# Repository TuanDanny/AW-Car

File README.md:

# AW-Car

Xe 4WD hai bên độc lập. **Web → Motion → SPI → Tang Nano9K → DRV8833** là
đường điều khiển trực tiếp. Brain chạy Xiaozhi, mic, loa và OLED, rồi gửi lệnh
AI sang Motion qua UART. Manual hoạt động qua AW-CAR tại `192.168.4.1`.
Wi-Fi router phục vụ Xiaozhi, OTA và log.

[Bản hiện hành, mốc nghiệm thu và phần cứng chờ bổ sung](docs/current-release.md)
ghi mã nguồn và mã firmware của cả ba board. `main` là nhánh chính thức.
`prototype-v1` và `prototype-v2` là hai mốc phục hồi.

| Thư mục | Nội dung |
| --- | --- |
| [esp](esp/README.md) | Firmware Brain, Motion và giao thức C++ dùng chung |
| [fpga](fpga/README.md) | SPI, PWM và encoder SystemVerilog trên Tang Nano9K |
| [schematic](schematic/README.md) | Bản vẽ đấu nối tham chiếu |
| [docs](docs/README.md) | Hướng dẫn, contract và lịch sử kiểm chứng |
| [data](data/README.md) | Vector giao thức và bằng chứng đã lọc |
| [utils](utils/README.md) | Build, kiểm tra, OTA và thu log |
| [test](test/README.md) | Kiểm thử host, trình duyệt và RTL |

Bắt đầu từ [Dashboard](docs/dashboard.md), [OTA và log](docs/ota-usage.md)
hoặc [hướng dẫn build](docs/build.md). Đọc [contract](docs/protocol.md)
trước khi đổi giao thức và [bảng chân đang chạy](docs/current-release.md#chân-cảm-biến-và-phần-cứng-chờ-bổ-sung)
trước khi đi dây.

## Bảng kết nối toàn mạch

Bảng V4 dưới đây đối chiếu với PCB và schematic **candidate** đang chỉnh tại
`schematic/pcb-in/ban-di-day-dang-do` trên máy làm việc ngày 26/11/2026.
PCB này còn đang đi dây và chưa được kiểm chứng hoàn chỉnh.\nPCB chính thức trên máy nằm trong thư mục `schematic/pcb-in/ban-di-day-dang-do`. Số `Pxx` là số
chân package FPGA của Tang Nano 9K, còn `GPIOxx` là GPIO ESP32-S3.

**Trạng thái V4:** source trên nhánh này sử dụng pinout PCB V4 ở SPI
Motion, encoder và các đầu ra DRV. Firmware V4 mới build cần được thử lại
trên đúng ba board trước khi xác nhận trùng với Flash trên xe.

### Nguồn

| Đầu nối hoặc nguồn | Kết nối V4 |
| --- | --- |
| U15 | Chân 1: +5,18 V từ DSN 1 cho Brain và Motion. Chân 2: GND. |
| U16 | Chân 1: +5,10 V từ DSN 2 cho Tang, MAX98357A và tải 5 V AUX. Chân 2: GND. |
| U18 | Chân 1: +3,3 V từ buck ngoại vi. Chân 2: GND. Cấp các module ngoại vi 3,3 V theo bảng dưới. |
| J9 | Chân 1: +VM từ pin 2S qua cầu chì F1 ngoài bo. Chân 2: GND. VM đến cả hai DRV. |
| GND | Âm pin, âm các buck, ba board và ngoại vi nối chung. Hai đầu ra dương 5 V và buck 3,3 V giữ riêng. |

Buck 3,3 V cấp ngoại vi, không cấp vào chân 3V3 hoặc GPIO ESP32-S3.
Ngắt nguồn 5 V ngoài của board trước khi cắm USB board đó.

### Brain và Motion

| Tín hiệu | Nối dây |
| --- | --- |
| Brain TX → Motion RX | Brain GPIO17 → Motion GPIO14 |
| Motion TX → Brain RX | Motion GPIO13 → Brain GPIO18 |
| INMP441 WS / SCK / SD | Brain GPIO4 / GPIO5 / GPIO6 |
| INMP441 VDD / GND / L/R | 3,3 V ngoại vi / GND / GND |
| OLED SDA / SCL | Brain GPIO41 / GPIO42. VCC 3,3 V ngoại vi và GND. |
| MAX98357A DIN / BCLK / LRC | Brain GPIO7 / GPIO15 / GPIO16 |
| MAX98357A VIN / GND | 5 V AUX / GND |
| Loa | Nối hai dây vào SPK+ và SPK− của MAX98357A. |
| VL53L0X SDA / SCL | Motion GPIO11 / GPIO12, VCC 3,3 V ngoại vi và GND |
| MPU SDA / SCL | Motion GPIO6 / GPIO7, VCC 3,3 V ngoại vi và GND |
| Mép trái / phải theo firmware main | Motion GPIO8 / GPIO9. Trên PCB V4 hai chân này đưa ra JXM1. |
| STBY hai DRV | Motion GPIO10 qua hai nhánh điện trở riêng tới STBY trái và phải |

GPIO17/18 của Motion được ghi nhận là hỏng trên board đã dùng. Nút BOOT
Brain là GPIO0, LED onboard Brain là GPIO48.

### SPI Motion → Tang

| Tín hiệu | Motion | Tang |
| --- | --- | --- |
| MOSI | GPIO42 | P25 |
| MISO | GPIO41 | P26 |
| SCLK | GPIO40 | P29 |
| CS | GPIO39 | P30 |

### Tang, DRV và encoder

| Tín hiệu | Chân Tang V4 |
| --- | --- |
| DRV trái IN1 / IN2 | P51 / P35 |
| DRV phải IN1 / IN2 | P31 / P32 |
| Encoder trái / phải qua chuyển mức | P49 / P48 |

Trên PCB V4, IN1 nối đến AIN1 và BIN1 cùng phía, IN2 nối đến AIN2 và BIN2.
Mỗi DRV có hai ngõ ra AO và BO cho hai motor của cùng bên. Mỗi encoder dùng
một OUT, qua bộ chuyển mức từ 5 V encoder sang mức tham chiếu 3,3 V của Tang.
Giắc encoder U10/U17 có thứ tự GND, 5 V AUX, OUT. Xác nhận thứ tự trên module
encoder thực tế trước khi cắm.

### Giắc mở rộng trên PCB V4

| Giắc | Thứ tự chân theo số pad |
| --- | --- |
| JXB1 — Brain 2×5 | 1 GPIO8, 2 GPIO9, 3 GPIO10, 4 GPIO11, 5 GPIO12, 6 GPIO13, 7 GPIO14, 8 GPIO21, 9 GPIO47, 10 GPIO1 |
| JXM1 — Motion 2×6 | 1 GND, 2 3V3 ngoại vi, 3 GPIO8, 4 GPIO9, 5 GPIO38, 6 GPIO5, 7 GND, 8 SDA ToF, 9 SCL ToF, 10 GND, 11 5V AUX, 12 3V3 ngoại vi |
| JXT1 — Tang 2×5 | 1 P27, 2 P28, 3 P33, 4 P34, 5 P40, 6 P41, 7 P42, 8 P53, 9 P54, 10 P56 |

JXB1 gồm 10 chân GPIO, lấy nguồn và GND từ giắc khác. SDA/SCL trên JXM1 dùng
chung bus ToF. Một số chân JXT1 dùng chung chức năng RGB LCD trên board Tang;
cần cấu hình RTL và xem xét thiết bị gắn trên board khi sử dụng.

### Siêu âm dự kiến trên PCB V4

| Vị trí | TRIG từ Motion | ECHO tới Motion |
| --- | --- | --- |
| Trước U19 | GPIO1 | GPIO15 qua chia áp |
| Trái U20 | GPIO2 | GPIO16 qua chia áp |
| Phải U21 | GPIO21 | GPIO4 qua chia áp |

Mỗi giắc có thứ tự 5 V AUX, TRIG, ECHO, GND. Mạch ECHO chia áp trước GPIO
ESP32-S3. Các kênh này là bố trí PCB dự kiến, cần kiểm tra firmware và module
thực tế trước khi sử dụng.

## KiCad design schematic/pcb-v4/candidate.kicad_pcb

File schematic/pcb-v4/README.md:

# PCB V4 đang phát triển

[Mở project KiCad](candidate.kicad_pro)

Bản sao từ PCB ủi được lưu trên máy ngày 25/11/2026. Thiết kế đang chỉnh,
chưa đủ điều kiện chế tạo. KiCad CLI lần kiểm tra tích hợp ghi nhận 93 lỗi
clearance, 4 lỗi đường biên, 2 sai khác schematic và các cảnh báo. Cần đối chiếu
bản chỉnh tay mới nhất và khắc phục DRC, sau đó thử điện và tải thực tế.

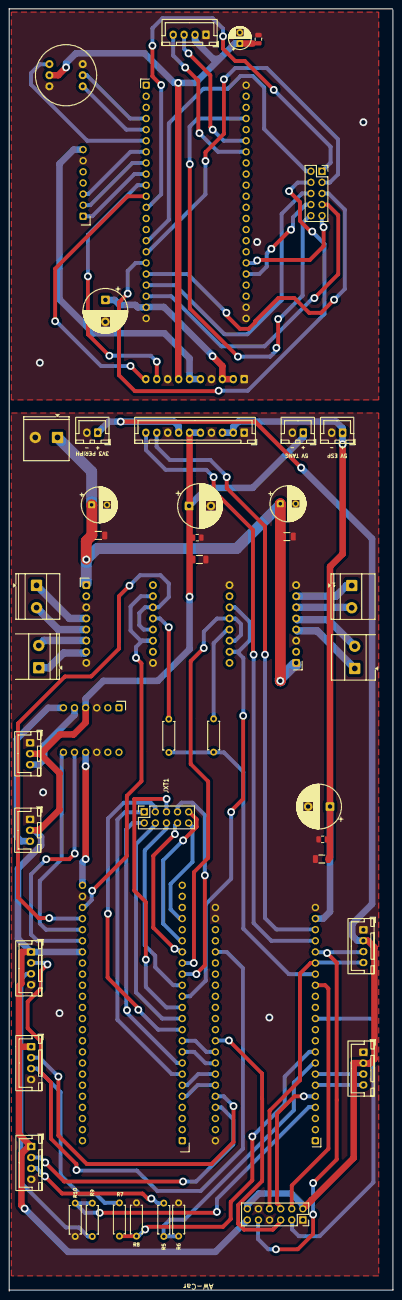
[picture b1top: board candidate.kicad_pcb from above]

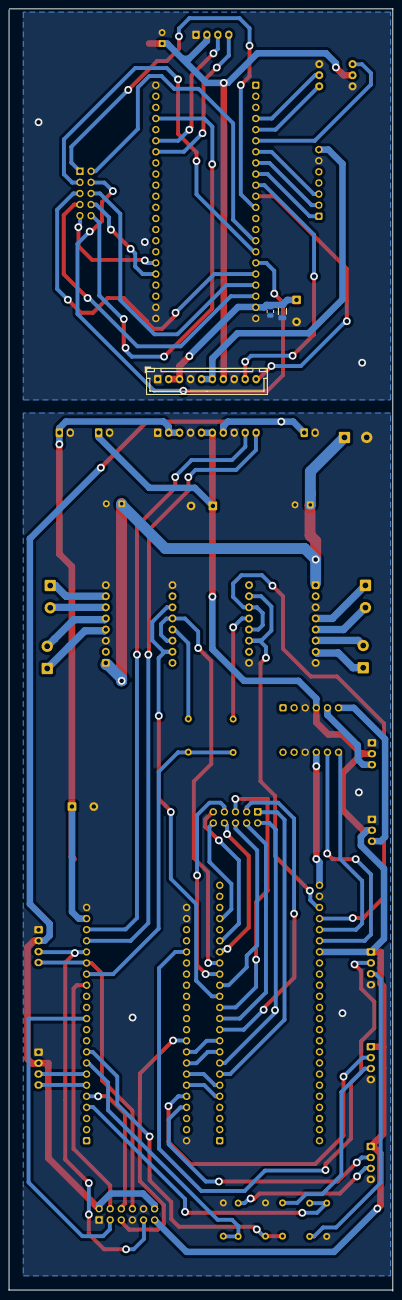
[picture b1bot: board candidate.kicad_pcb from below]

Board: 2 copper layers, 87.9 x 293.2 mm, 52 parts (3 on the bottom side), 82 nets.

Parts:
C1, C2, C3: 1000uF/16V; CP_Radial_D10.0mm_P5.00mm
C4, C5, C6: 10uF/16V; C_1206_3216Metric
C7, C8, C9: 100nF/16V; C_0805_2012Metric
C10: 47uF/10V; CP_Radial_D5.0mm_P2.50mm
C11: 100nF/10V; C_0805_2012Metric
C12, C14: 220uF/25V; CP_Radial_D8.0mm_P3.50mm
C13, C15: 10uF/25V; C_1206_3216Metric
J9: VM <= 8.4V; TerminalBlock_Phoenix_MKDS-1,5-2-5.08_1x02_P5.08mm_Horizont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
J11: M1 LF; TerminalBlock_Phoenix_MKDS-1,5-2-5.08_1x02_P5.08mm_Horizont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
J12: M2 LR; TerminalBlock_Phoenix_MKDS-1,5-2-5.08_1x02_P5.08mm_Horizont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
J13: M3 RF; TerminalBlock_Phoenix_MKDS-1,5-2-5.08_1x02_P5.08mm_Horizont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
J14: M4 RR; TerminalBlock_Phoenix_MKDS-1,5-2-5.08_1x02_P5.08mm_Horizont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
JBT1, JBT2: JST-XH 10P INTERTIER; JST_XH_B10B-XH-A_1x10_P2.50mm_Vertical
JOLED1: OLED_REMOTE_4P_3V3; JST_XH_B4B-XH-A_1x04_P2.50mm_Vertical
JXB1: BRAIN_EXP_GPIO_10P; PinSocket_2x05_P2.54mm_Vertical
JXM1: MOTION_EXP_GPIO_12P; PinSocket_2x06_P2.54mm_Vertical
JXT1: TANG_EXP_GPIO_10P; PinSocket_2x05_P2.54mm_Vertical
R1, R2: 1k; R_Axial_DIN0207_L6.3mm_D2.5mm_P7.62mm_Horizontal
R5, R7, R9: 10k; R_Axial_DIN0207_L6.3mm_D2.5mm_P7.62mm_Horizontal
R6, R8, R10: 15k; R_Axial_DIN0207_L6.3mm_D2.5mm_P7.62mm_Horizontal
U1: BRAIN; ESP32_S3_DevKitC_2x22
U2: MOTION; ESP32_S3_DevKitC_2x22
U3: TANG NANO 9K; Tang_Nano_9K_2x24
U4: DRV LEFT; DRV8833_V318_2x08
U5: DRV RIGHT; DRV8833_V318_2x08
U6: INMP441_SOCKET_2x3_VERIFY; INMP441_Module_2x03_Row7.62_14mm_PROVISIONAL
U7: MAX98357A; MAX98357A_1x07
U9: LEVEL SHIFT; Level_Shifter_2x06
U10: ENC R 5V; JST_XH_B3B-XH-A_1x03_P2.50mm_Vertical
U11: MPU; JST_XH_B4B-XH-A_1x04_P2.50mm_Vertical
U12: TOF; JST_XH_B4B-XH-A_1x04_P2.50mm_Vertical
U15: +5V ESP; JST_XH_B2B-XH-A_1x02_P2.50mm_Vertical
U16: +5V TANG/SPK; JST_XH_B2B-XH-A_1x02_P2.50mm_Vertical
U17: ENC L 5V; JST_XH_B3B-XH-A_1x03_P2.50mm_Vertical
U18: +3V3 PERIPH; JST_XH_B2B-XH-A_1x02_P2.50mm_Vertical
U19, U20, U21: HC-SR04 VCC TRIG ECHO GND; JST_XH_B4B-XH-A_1x04_P2.50mm_Vertical

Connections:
BOT_3V3_PERIPH: JBT2.7 (3V3_ngoại_vi), JXM1.2 (3V3_PERIPH_2), JXM1.12 (3V3_PERIPH_16), U11.2 (VCC_3V3), U12.2 (VIN_3V3), U18.1 (VIN+)
BOT_3V3_TANG: U3.B24 (3V3), U9.B04 (LV_3V3)
BOT_5V_AUX: C3.1, C6.1, C9.1, JBT2.5 (5V_AUX), JBT2.6 (5V_AUX), JXM1.11 (5V_AUX_14), U3.B18 (5V), U9.A04 (HV_5V), U10.2 (VCC_5V), U16.1 (VIN+), U17.2 (VCC_5V), U19.1 (VCC_5V), U20.1 (VCC_5V), U21.1 (VCC_5V)
BOT_5V_ESP_SUPPLY: C2.1, C5.1, C8.1, JBT2.2 (5V_ESP), JBT2.3 (5V_ESP), U2.A21 (5V), U15.1 (VIN+)
BOT_BM_BRAIN_TX: JBT2.9 (Brain_TX), U2.A20 (GPIO14)
BOT_BM_MOTION_TX: JBT2.10 (Motion_TX), U2.A19 (GPIO13)
BOT_ENC_L_3V3: U3.B20 (P49), U9.B06 (LV1)
BOT_ENC_L_5V: U9.A06 (HV1), U17.3 (OUT)
BOT_ENC_R_3V3: U3.B19 (P48), U9.B05 (LV2)
BOT_ENC_R_5V: U9.A05 (HV2), U10.3 (OUT)
BOT_EXP_GPIO5: JXM1.6 (GPIO5_9), U2.A05 (GPIO5)
BOT_EXP_GPIO8: JXM1.3 (GPIO8_3), U2.A12 (GPIO8)
BOT_EXP_GPIO9: JXM1.4 (GPIO9_4), U2.A15 (GPIO9)
BOT_EXP_GPIO38: JXM1.5 (GPIO38_7), U2.B10 (GPIO38)
BOT_GND: C2.2, C3.2, C5.2, C6.2, C8.2, C9.2, C12.2, C13.2, C14.2, C15.2, J9.2 (GND), JBT2.1 (GND), JBT2.4 (GND), JBT2.8 (GND), JXM1.1 (GND_1), JXM1.7 (GND_10), JXM1.10 (GND_13), R6.2, R8.2, R10.2, U2.A22 (GND), U2.B01 (GND), U2.B21 (GND), U2.B22 (GND), U3.B23 (GND), U4.A03 (GND), U4.A08 (GND), U4.B08 (GND), U5.A03 (GND), U5.A08 (GND), U5.B08 (GND), U9.A03 (GND), U9.B03 (GND), U10.1 (GND), U11.1 (GND), U12.1 (GND), U15.2 (GND), U16.2 (GND), U17.1 (GND), U18.2 (GND), U19.4 (GND), U20.4 (GND), U21.4 (GND)
BOT_L_AO1: J11.1 (AO1), U4.A04 (AO1)
BOT_L_AO2: J11.2 (AO2), U4.A05 (AO2)
BOT_L_BO1: J12.1 (BO1), U4.A07 (BO1)
BOT_L_BO2: J12.2 (BO2), U4.A06 (BO2)
BOT_L_IN1: U3.A17 (P51), U4.B03 (AIN1), U4.B05 (BIN1)
BOT_L_IN2: U3.A14 (P35), U4.B02 (AIN2), U4.B06 (BIN2)
BOT_MPU_SCL: U2.A07 (GPIO7), U11.3 (SCL)
BOT_MPU_SDA: U2.A06 (GPIO6), U11.4 (SDA)
BOT_R_AO1: J13.1 (AO1), U5.A04 (AO1)
BOT_R_AO2: J13.2 (AO2), U5.A05 (AO2)
BOT_R_BO1: J14.1 (BO1), U5.A07 (BO1)
BOT_R_BO2: J14.2 (BO2), U5.A06 (BO2)
BOT_R_IN1: U3.B21 (P31), U5.B03 (AIN1), U5.B05 (BIN1)
BOT_R_IN2: U3.B22 (P32), U5.B02 (AIN2), U5.B06 (BIN2)
BOT_SPI_CS_N: U2.B09 (GPIO39), U3.A10 (P30)
BOT_SPI_MISO: U2.B07 (GPIO41), U3.A06 (P26)
BOT_SPI_MOSI: U2.B06 (GPIO42), U3.A05 (P25)
BOT_SPI_SCLK: U2.B08 (GPIO40), U3.A09 (P29)
BOT_STBY_COMMAND: R1.1, R2.1, U2.A16 (GPIO10)
BOT_STBY_L: R1.2, U4.B04 (STBY_/_nSLEEP)
BOT_STBY_R: R2.2, U5.B04 (STBY_/_nSLEEP)
BOT_TANG_P27: JXT1.1 (P27), U3.A07 (P27)
BOT_TANG_P28: JXT1.2 (P28), U3.A08 (P28)
BOT_TANG_P33: JXT1.3 (P33), U3.A11 (P33)
BOT_TANG_P34: JXT1.4 (P34), U3.A12 (P34)
BOT_TANG_P40: JXT1.5 (P40), U3.A13 (P40)
BOT_TANG_P41: JXT1.6 (P41), U3.A15 (P41)
BOT_TANG_P42: JXT1.7 (P42), U3.A16 (P42)
BOT_TANG_P53: JXT1.8 (P53), U3.A18 (P53)
BOT_TANG_P54: JXT1.9 (P54), U3.A19 (P54)
BOT_TANG_P56: JXT1.10 (P56), U3.A21 (P56)
BOT_TOF_SCL: JXM1.9 (TOF_SCL_12), U2.A18 (GPIO12), U12.3 (SCL)
BOT_TOF_SDA: JXM1.8 (TOF_SDA_11), U2.A17 (GPIO11), U12.4 (SDA)
BOT_US_F_ECHO: R5.2, R6.1, U2.A08 (GPIO15)
BOT_US_F_ECHO_RAW: R5.1, U19.3 (ECHO)
BOT_US_F_TRIG: U2.B04 (GPIO1), U19.2 (TRIG)
BOT_US_L_ECHO: R7.2, R8.1, U2.A09 (GPIO16)
BOT_US_L_ECHO_RAW: R7.1, U20.3 (ECHO)
BOT_US_L_TRIG: U2.B05 (GPIO2), U20.2 (TRIG)
BOT_US_R_ECHO: R9.2, R10.1, U2.A04 (GPIO4)
BOT_US_R_ECHO_RAW: R9.1, U21.3 (ECHO)
BOT_US_R_TRIG: U2.B18 (GPIO21), U21.2 (TRIG)
BOT_VM_8V4: C12.1, C13.1, C14.1, C15.1, J9.1 (+_2S_sau_F1), U4.A01 (VM), U5.A01 (VM)
TOP_3V3_PERIPH: C10.1, C11.1, JBT1.7 (3V3_ngoại_vi), JOLED1.2 (VCC_3V3), U6.2 (VDD)
TOP_5V_AUX: JBT1.5 (5V_AUX), JBT1.6 (5V_AUX), U7.A07 (VIN_5V)
TOP_5V_ESP_SUPPLY: C1.1, C4.1, C7.1, JBT1.2 (5V_ESP), JBT1.3 (5V_ESP), U1.A21 (5V)
TOP_AMP_BCLK: U1.A08 (GPIO15), U7.A02 (BCLK)
TOP_AMP_DIN: U1.A07 (GPIO7), U7.A03 (DIN)
TOP_AMP_LRC: U1.A09 (GPIO16), U7.A01 (LRC)
TOP_BM_BRAIN_TX: JBT1.9 (Brain_TX), U1.A10 (GPIO17)
TOP_BM_MOTION_TX: JBT1.10 (Motion_TX), U1.A11 (GPIO18)
TOP_EXP_GPIO1: JXB1.10 (GPIO1), U1.B04 (GPIO1)
TOP_EXP_GPIO8: JXB1.1 (GPIO8), U1.A12 (GPIO8)
TOP_EXP_GPIO9: JXB1.2 (GPIO9), U1.A15 (GPIO9)
TOP_EXP_GPIO10: JXB1.3 (GPIO10), U1.A16 (GPIO10)
TOP_EXP_GPIO11: JXB1.4 (GPIO11), U1.A17 (GPIO11)
TOP_EXP_GPIO12: JXB1.5 (GPIO12), U1.A18 (GPIO12)
TOP_EXP_GPIO13: JXB1.6 (GPIO13), U1.A19 (GPIO13)
TOP_EXP_GPIO14: JXB1.7 (GPIO14), U1.A20 (GPIO14)
TOP_EXP_GPIO21: JXB1.8 (GPIO21), U1.B18 (GPIO21)
TOP_EXP_GPIO47: JXB1.9 (GPIO47), U1.B17 (GPIO47)
TOP_GND: C1.2, C4.2, C7.2, C10.2, C11.2, JBT1.1 (GND), JBT1.4 (GND), JBT1.8 (GND), JOLED1.1 (GND), U1.A22 (GND), U1.B01 (GND), U1.B21 (GND), U1.B22 (GND), U6.1 (GND), U6.6 (L/R), U7.A06 (GND)
TOP_MIC_BCLK: U1.A05 (GPIO5), U6.4 (BCLK)
TOP_MIC_SD: U1.A06 (GPIO6), U6.3 (SD)
TOP_MIC_WS: U1.A04 (GPIO4), U6.5 (WS)
TOP_OLED_SCL: JOLED1.3 (SCL), U1.B06 (GPIO42)
TOP_OLED_SDA: JOLED1.4 (SDA), U1.B07 (GPIO41)
